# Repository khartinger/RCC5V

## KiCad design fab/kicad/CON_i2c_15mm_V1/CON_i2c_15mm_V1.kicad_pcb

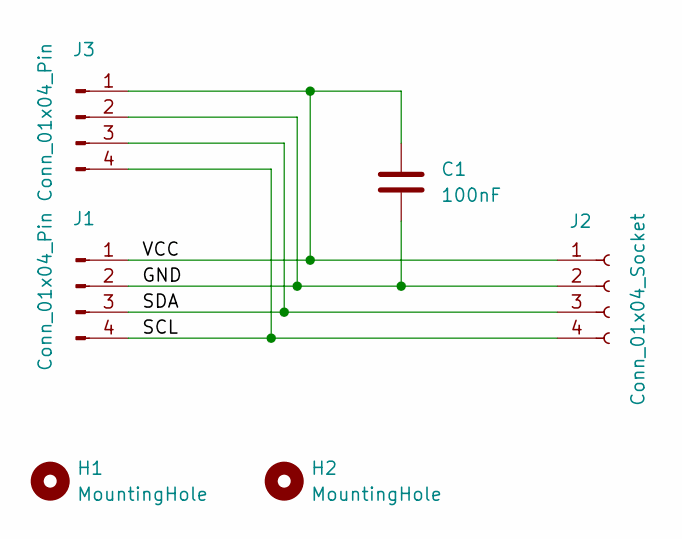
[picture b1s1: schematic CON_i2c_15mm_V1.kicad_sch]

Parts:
C1: 100nF; C_L4mm_D3mm_P2.54mm_kh
H1, H2: MountingHole; MountingHole_2.2mm_M2_Pad_TopBottom_kh
J1, J3: Conn_01x04_Pin; PinSocket_1x04_P2.54mm_Vertical_kh
J2: Conn_01x04_Socket; PinSocket_1x04_P2.54mm_Vertical_kh

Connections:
/GND: C1.2, J1.2, J2.2, J3.2
/SCL: J1.4, J2.4, J3.4
/SDA: J1.3, J2.3, J3.3
/VCC: C1.1, J1.1, J2.1, J3.1

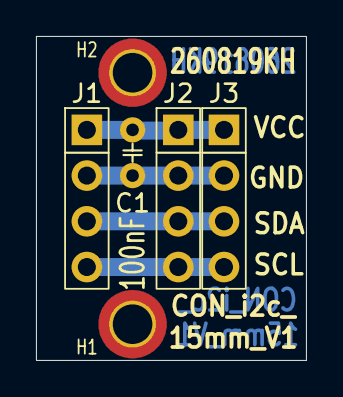
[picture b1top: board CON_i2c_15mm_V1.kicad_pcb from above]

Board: 2 copper layers, 15.0 x 18.0 mm, 6 parts (0 on the bottom side), 4 nets.

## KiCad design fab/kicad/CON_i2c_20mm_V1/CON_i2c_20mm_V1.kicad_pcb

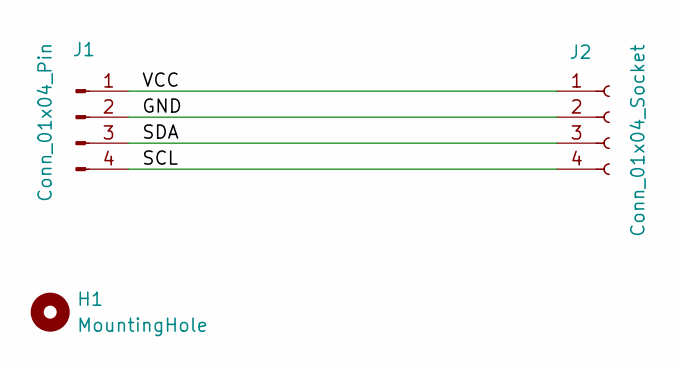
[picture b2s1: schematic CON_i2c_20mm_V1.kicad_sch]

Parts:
H1: MountingHole; MountingHole_2.2mm_M2_Pad_TopBottom_kh
J1: Conn_01x04_Pin; PinSocket_1x04_P2.54mm_Vertical_kh
J2: Conn_01x04_Socket; PinSocket_1x04_P2.54mm_Vertical_kh

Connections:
/GND: J1.2, J2.2
/SCL: J1.4, J2.4
/SDA: J1.3, J2.3
/VCC: J1.1, J2.1

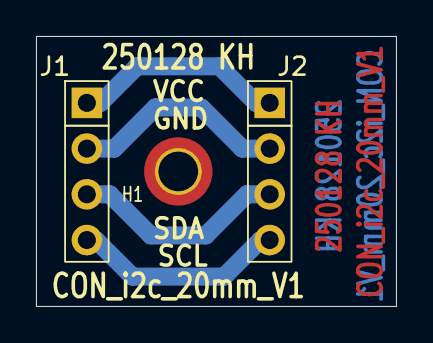
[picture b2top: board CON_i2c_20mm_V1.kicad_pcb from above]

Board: 2 copper layers, 20.0 x 15.0 mm, 3 parts (0 on the bottom side), 4 nets.

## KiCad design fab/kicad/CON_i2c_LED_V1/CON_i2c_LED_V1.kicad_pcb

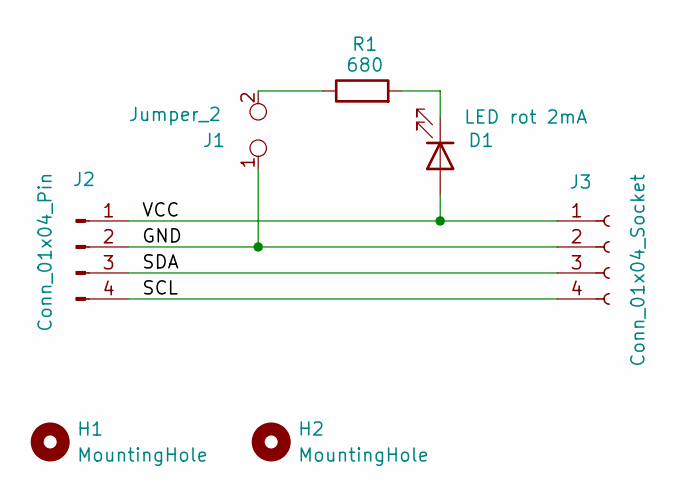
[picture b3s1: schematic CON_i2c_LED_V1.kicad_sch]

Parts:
D1: LED rot 2mA; LED_D3.0mm
H1, H2: MountingHole; MountingHole_2.2mm_M2_Pad_TopBottom_kh
J1: Jumper_2; PinSocket_1x02_P2.54mm_Vertical_kh
J2: Conn_01x04_Pin; PinSocket_1x04_P2.54mm_Vertical_kh
J3: Conn_01x04_Socket; PinSocket_1x04_P2.54mm_Vertical_kh
R1: 680; R_Axial_DIN0204_L3.6mm_D1.6mm_P2.54mm_Vertical_kh

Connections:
/GND: J1.1, J2.2, J3.2
/SCL: J2.4, J3.4
/SDA: J2.3, J3.3
/VCC: D1.2 (A), J2.1, J3.1
unnamed: D1.1 (K), R1.2
unnamed: J1.2, R1.1

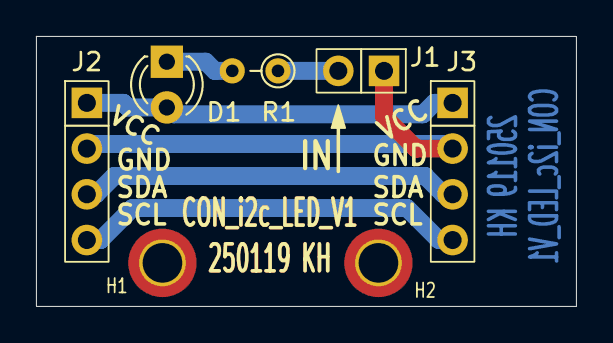
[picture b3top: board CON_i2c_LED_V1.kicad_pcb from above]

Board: 2 copper layers, 30.0 x 15.0 mm, 7 parts (0 on the bottom side), 6 nets.

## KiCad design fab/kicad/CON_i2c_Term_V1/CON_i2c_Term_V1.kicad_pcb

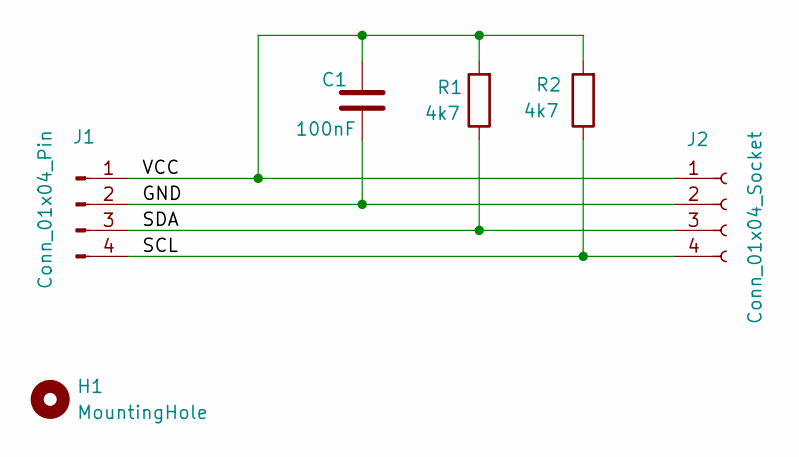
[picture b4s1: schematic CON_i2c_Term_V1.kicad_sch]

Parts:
C1: 100nF; C_Disc_D3.0mm_W1.6mm_P2.50mm
H1: MountingHole; MountingHole_2.2mm_M2_Pad_TopBottom_kh
J1: Conn_01x04_Pin; PinSocket_1x04_P2.54mm_Vertical_kh
J2: Conn_01x04_Socket; PinSocket_1x04_P2.54mm_Vertical_kh
R1: 4k7; R_Axial_P5.08_Vertical_kh
R2: 4k7; R_Axial_P7.62_Vertical_kh

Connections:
/GND: C1.2, J1.2, J2.2
/SCL: J1.4, J2.4, R2.1
/SDA: J1.3, J2.3, R1.1
/VCC: C1.1, J1.1, J2.1, R1.2, R2.2

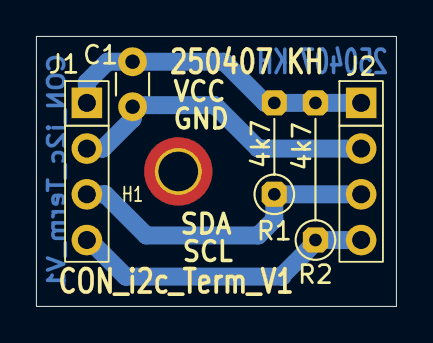
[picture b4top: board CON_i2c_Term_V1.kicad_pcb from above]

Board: 2 copper layers, 20.0 x 15.0 mm, 6 parts (0 on the bottom side), 4 nets.

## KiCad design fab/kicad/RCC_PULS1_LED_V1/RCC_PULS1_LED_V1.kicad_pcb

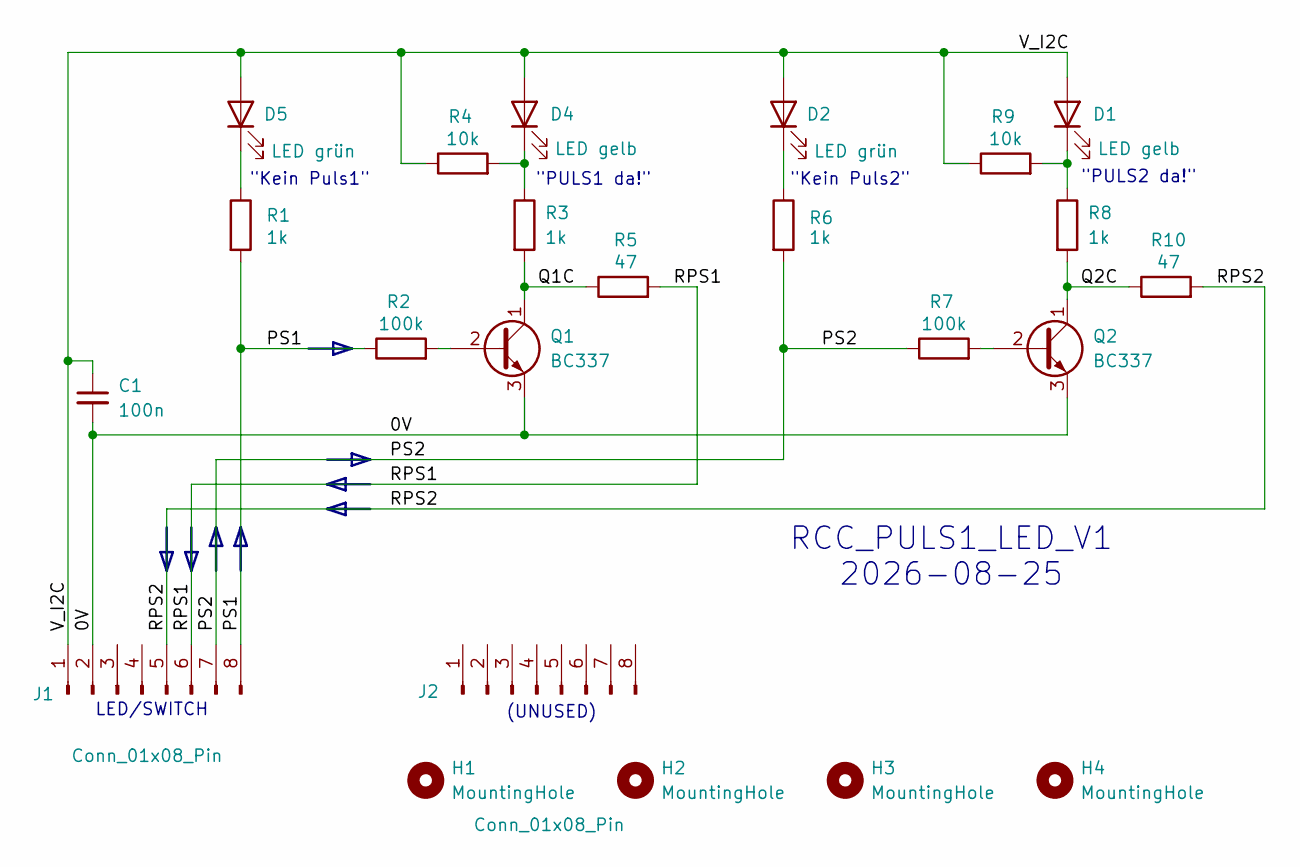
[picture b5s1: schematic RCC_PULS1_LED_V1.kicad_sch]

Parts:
C1: 100n; C_L4mm_D3mm_P2.54mm_kh
D1, D4: LED gelb; LED_D3.0mm
D2, D5: LED grün; LED_D3.0mm
H1, H2, H3, H4: MountingHole; MountingHole_2.2mm_M2_Pad_TopBottom_kh
J1, J2: Conn_01x08_Pin; PinSocket_1x08_P2.54mm_Vertical_11mm_kh
Q1, Q2: BC337; TO-92_Inline_Wide_custom
R1, R6, R8: 1k; R_Axial_DIN0204_L3.6mm_D1.6mm_P10,16mm_Horizontal
R2: 100k; R_Axial_DIN0204_L3.6mm_D1.6mm_P3.81mm_Vertical_kh
R3: 1k; R_Axial_DIN0204_L3.6mm_D1.6mm_P2.54mm_Vertical_kh
R4, R9: 10k; R_Axial_DIN0204_L3.6mm_D1.6mm_P2.54mm_Vertical_kh
R5: 47; R_Axial_DIN0204_L3.6mm_D1.6mm_P2.54mm_Vertical_kh
R7: 100k; R_Axial_DIN0204_L3.6mm_D1.6mm_P7.62mm_Horizontal
R10: 47; R_Axial_DIN0204_L3.6mm_D1.6mm_P2.54mm_Vertical

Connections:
/0V: C1.2, J1.2, Q1.3 (E), Q2.3 (E)
/PS1: J1.8, R1.2, R2.1
/PS2: J1.7, R6.2, R7.1
/Q1C: Q1.1 (C), R3.2, R5.1
/Q2C: Q2.1 (C), R8.2, R10.1
/RPS1: J1.6, R5.2
/RPS2: J1.5, R10.2
/V_I2C: C1.1, D1.2 (A), D2.2 (A), D4.2 (A), D5.2 (A), J1.1, R4.1, R9.1
unnamed: D1.1 (K), R8.1, R9.2
unnamed: D2.1 (K), R6.1
unnamed: D4.1 (K), R3.1, R4.2
unnamed: D5.1 (K), R1.1
unnamed: Q1.2 (B), R2.2
unnamed: Q2.2 (B), R7.2

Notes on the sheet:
LED/SWITCH
(UNUSED)
RCC_PULS1_LED_V1 2026-08-25
"PULS2 da!"
"PULS1 da!"
"Kein Puls2"
"Kein Puls1"

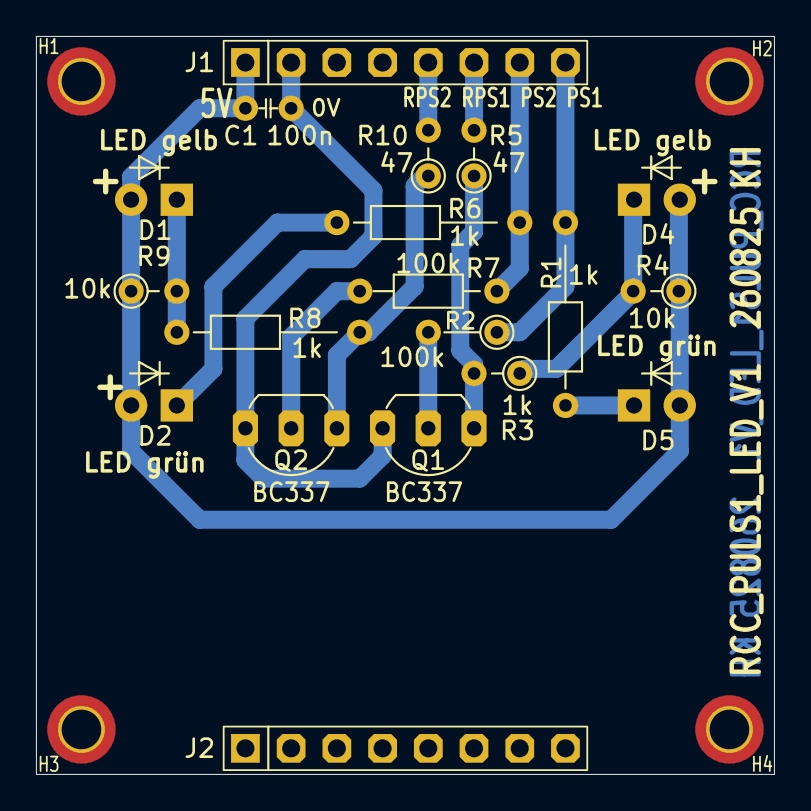
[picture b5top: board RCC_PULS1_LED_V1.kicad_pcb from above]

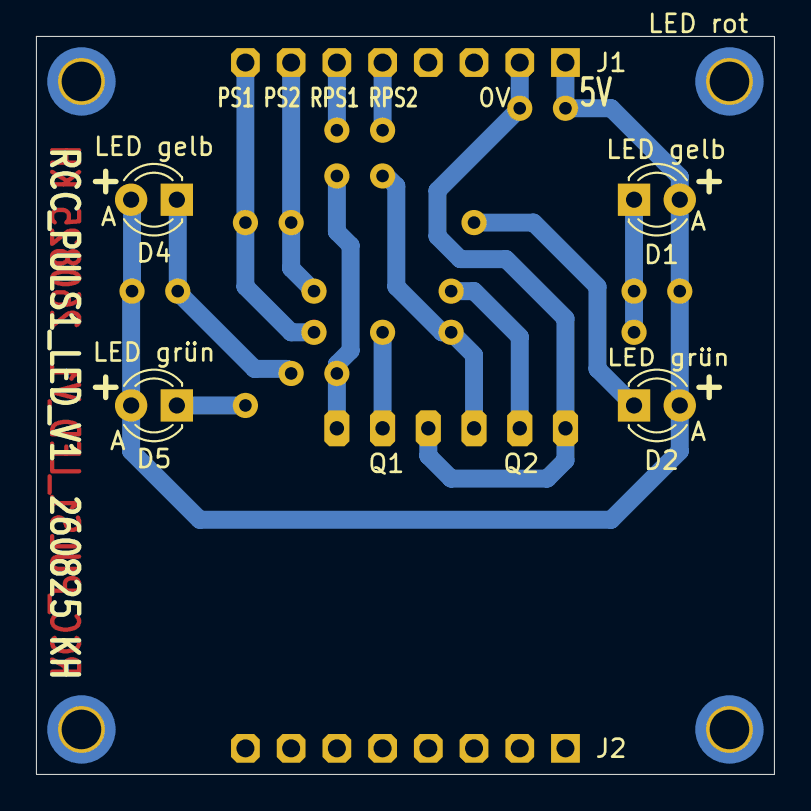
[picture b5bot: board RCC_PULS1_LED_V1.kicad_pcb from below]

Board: 2 copper layers, 41.0 x 41.0 mm, 23 parts (4 on the bottom side), 14 nets.
